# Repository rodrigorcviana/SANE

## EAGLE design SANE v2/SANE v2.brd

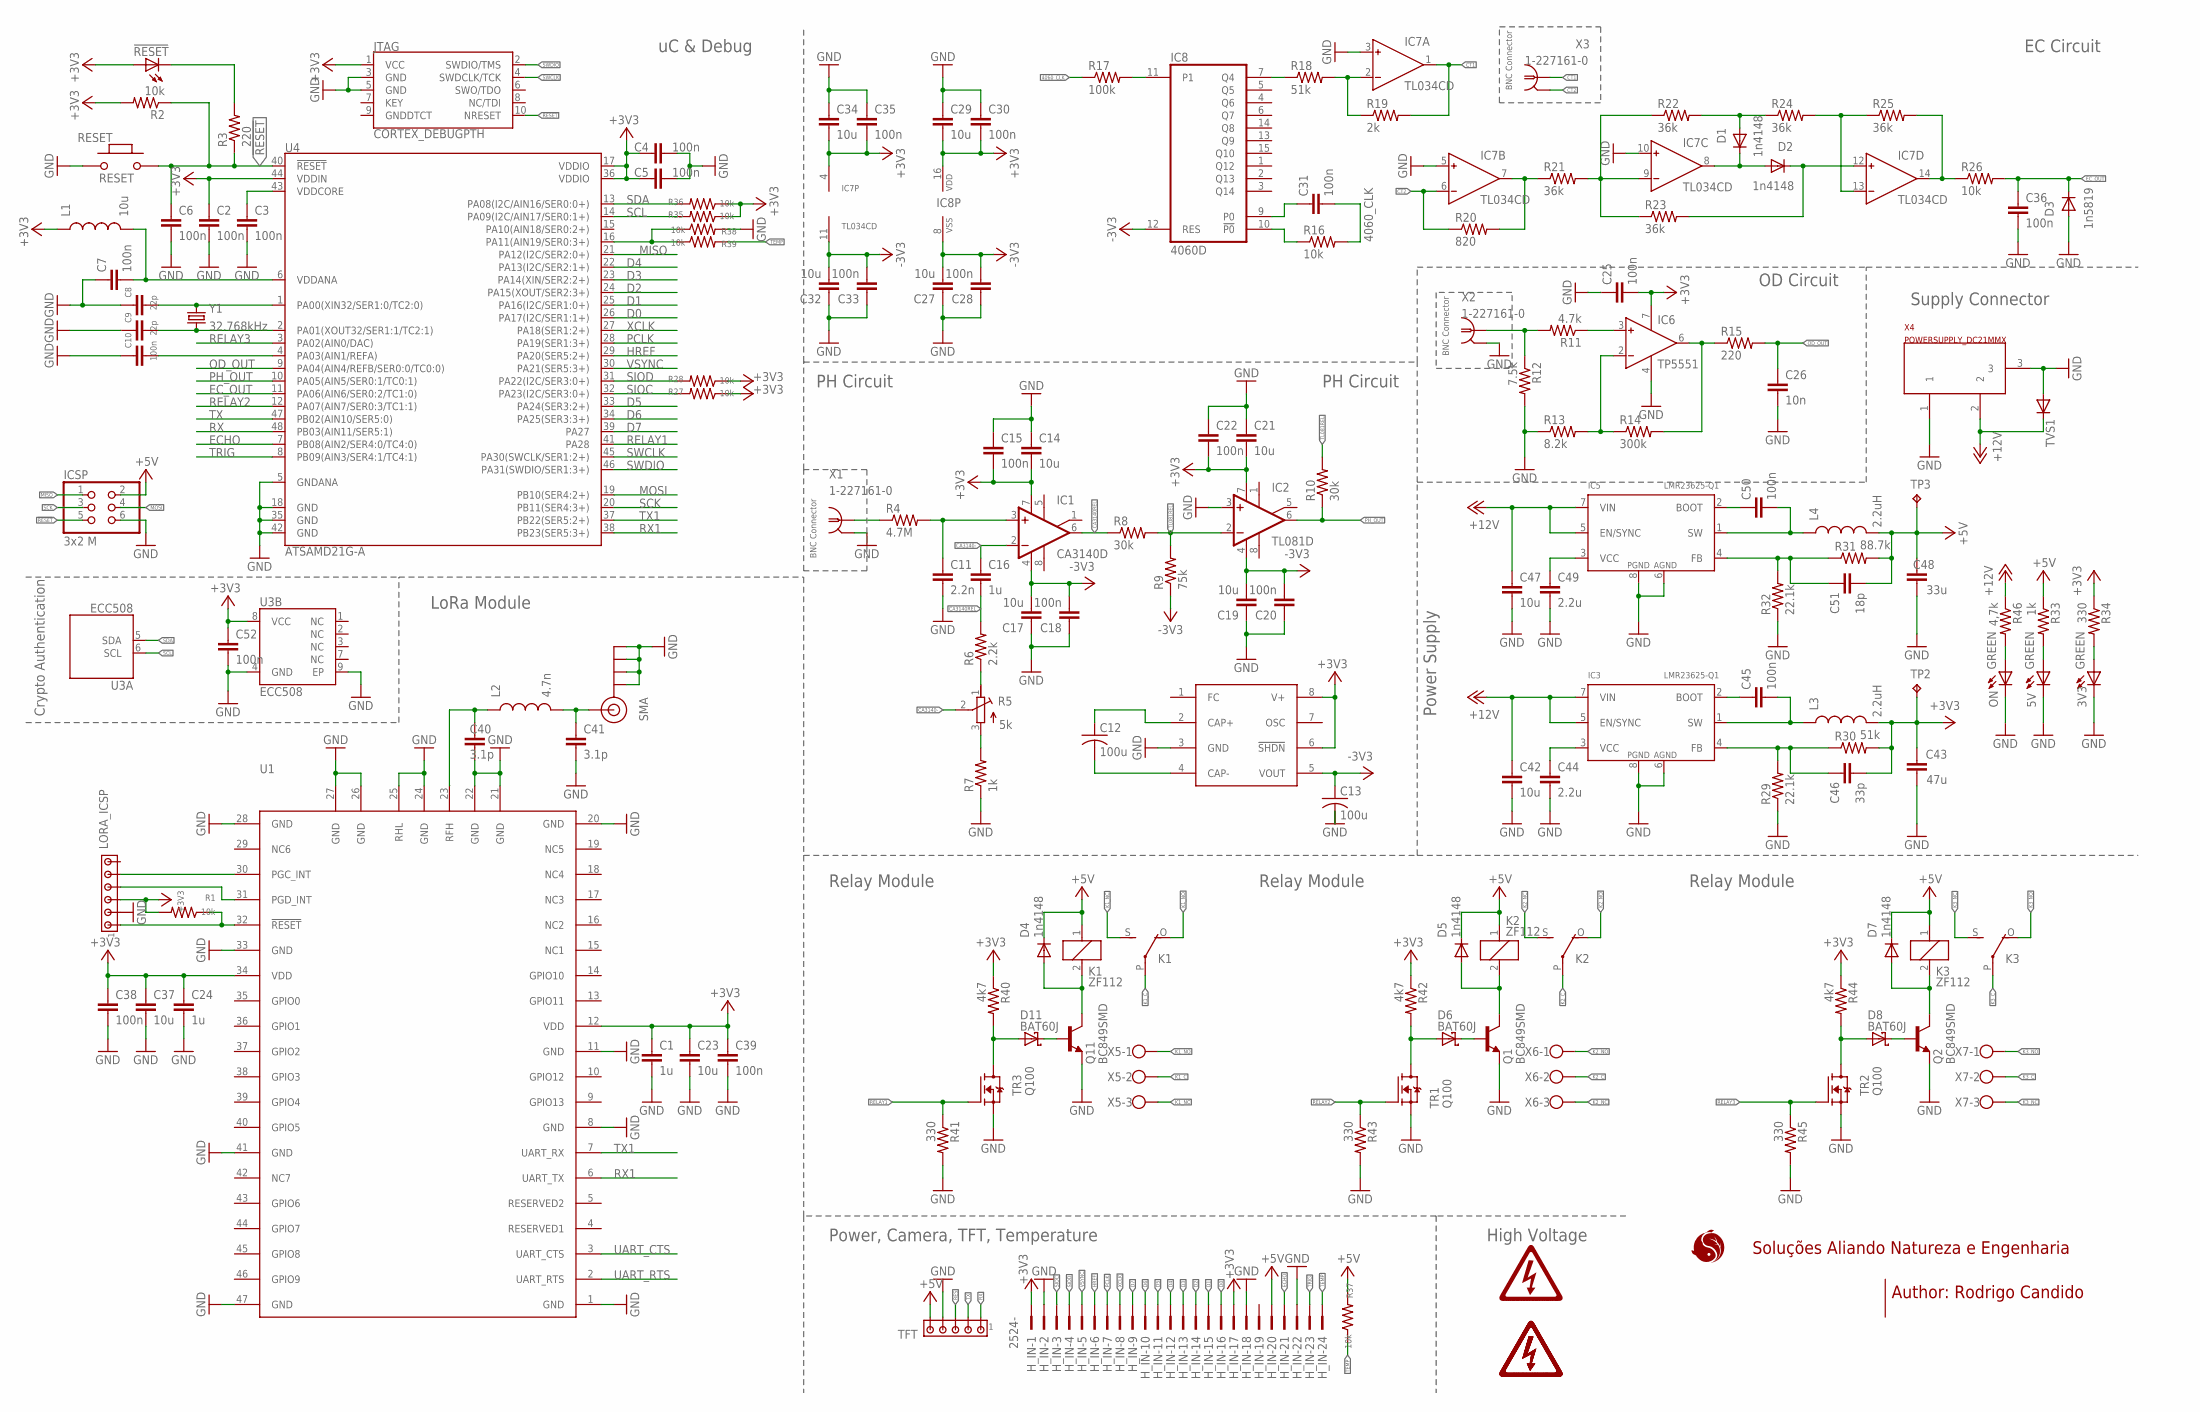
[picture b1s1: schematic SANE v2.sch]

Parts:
3V3, 5V: GREEN; CHIP-LED0805
!RESET: LEDCHIPLED_0805; CHIPLED_0805
C1, C16, C24: 1u; C1206
C2, C3, C4, C5, C6, C7, C10, C15, C18, C20, C22, C25, C28, C30, C31, C33, C35, C36, C38, C39, C45, C50, C52: 100n; C0805
C8, C9: 22p; C0805
C11: 2.2n; C0805
C12, C13: 100u; C1206
C14, C17, C19, C21, C23, C27, C29, C32, C34, C37, C42, C47: 10u; C1206
C26: 10n; C0805
C40, C41: 3.1p; C0603
C43: 47u; C1206
C44, C49: 2.2u; C0805
C46: 33p; C0805
C48: 33u; C1206
C51: 18p; C0805
D1, D2, D4, D5, D7: 1n4148; SOD123
D3: 1n5819; SOD123
D6, D8, D11: BAT60J; SOD323_ST
H_IN: 2524-; PAK100/2500-24
IC1: CA3140D; SO08
IC2: TL081D; SO08
IC3, IC5: LMR23625-Q1; SO08
IC4: TC1121COA; SO8
IC6: TP5551; SO8
IC7: TL034CD; SO14
IC8: 4060D; SO16
ICSP: 3x2 M; 2X03
JTAG: CORTEX_DEBUGPTH; 2X5-PTH-1.27MM
K1, K2, K3: ZF112
L1: 10u; 0603
L2: 4.7n; 0603
L3, L4: 2.2uH; L-NR3010
LORA_ICSP: MTA06-100; 10X06MTA
ON: GREEN; CHIP-LED0805
Q1, Q2, Q11: BC849SMD; SOT23-BEC
R1, R2, R16, R26, R27, R28, R35, R36, R37, R38, R39: 10k; R0805
R3, R15: 220; R0805
R4: 4.7M; R0805
R5: 5k; RTRIMT93YA
R6: 2.2k; R0805
R7, R33: 1k; R0805
R8, R10: 30k; R0805
R9: 75k; R0805
R11: 4.7k; R0805
R12: 7.5k; R0805
R13: 8.2k; R0805
R14: 300k; R0805
R17: 100k; R0805
R18: 51k; R0805
R19: 2k; R0805
R20: 820; R0805
R21, R22, R23, R24, R25: 36k; R0805
R29, R32: 22.1k; R0603
R30: 51k; R0603
R31: 88.7k; R0603
R34, R41, R43, R45: 330; R0805
R40, R42, R44: 4k7; R0805
R46: 4,7k; R0805
RESET: RESET; SMD_157SW
SMA_GPS: SMA_EDGE; SMA-EDGE
TFT: MTA05-100; 10X05MTA
TP2, TP3: TPPAD1-13; P1-13
TR1, TR2, TR3: Q100; SOT-23
TVS1: DIODE-SOD123; SOD123
U1: RN2483/RN2903
U3: ECC508; SON50P300X200X60-9N-EP160X140
U4: ATSAMD21G-A; TQFP-48
U$1, U$2, U$9: SHOCK
U$3: LOGO-SANE
X1, X2, X3: 1-227161-0; AMP_227161
X4: POWERSUPPLY_DC21MMX; POWERSUPPLY_DC-21MM
X5, X6, X7: W237-103
Y1: 32.768kHz; CRYSTAL-SMD-3.2X1.5MM

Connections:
4060_CLK: C31.2, R16.2, R17.1
!RESET: C6.1, ICSP.5, JTAG.10 (NRESET), R2.1, R3.1, RESET.2, U4.40 (!RESET!)
+3V3: !RESET.A, C1.1, C2.1, C4.1, C5.1, C14.2, C15.2, C21.2, C22.2, C23.1, C24.1, C25.2, C29.2, C30.2, C34.2, C35.2, C37.1, C38.1, C39.1, C43.2, C46.2, C52.1, H_IN.1, H_IN.17, IC1.7 (V+), IC2.7 (V+), IC4.6 (!SHDN), IC4.8 (V+), IC6.7 (V+), IC7.4 (V+), IC8.16 (VDD), JTAG.1 (VCC), L1.1, L3.P$2 (2), LORA_ICSP.3, R1.2, R2.2, R27.1, R28.1, R30.2, R34.1, R35.1, R36.1, R40.1, R42.1, R44.1, TP2.TP, U1.12 (VDD), U1.34 (VDD), U3.8 (VCC), U4.17 (VDDIO), U4.36 (VDDIO), U4.44 (VDDIN)
+5V: C48.2, C51.2, D4.C, D5.C, D7.C, H_IN.20, ICSP.2, K1.1, K2.1, K3.1, L4.P$2 (2), R31.2, R33.1, R37.2, TFT.5, TP3.TP
+12V: C42.1, C47.1, IC3.5 (EN/SYNC), IC3.7 (VIN), IC5.5 (EN/SYNC), IC5.7 (VIN), R46.1, TVS1.C, X4.2
-3V3: C13.1, C17.2, C18.2, C19.2, C20.2, C27.2, C28.2, C32.2, C33.2, IC1.4 (V-), IC2.4 (V-), IC4.5 (VOUT), IC7.11 (V-), IC8.8 (VSS), IC8.12 (RES), R9.1
CA3140-: C16.1, IC1.2 (-IN), R5.2 (S)
CA3140REL: C16.2, IC1.6 (OUT), R6.2, R8.1
CT1: IC7.1 (OUT), R19.2, X3.1
CT2: IC7.6 (IN-), R20.1, X3.2
D0: H_IN.16, U4.26 (PA17(I2C/SER1:1+))
D1: H_IN.15, U4.25 (PA16(I2C/SER1:0+))
D2: H_IN.14, U4.24 (PA15(XOUT/SER2:3+))
D3: H_IN.13, U4.23 (PA14(XIN/SER2:2+))
D4: H_IN.12, U4.22 (PA13(I2C/SER2:1+))
D5: H_IN.11, U4.33 (PA24(SER3:2+))
D6: H_IN.10, U4.34 (PA25(SER3:3+))
D7: H_IN.9, U4.39 (PA27)
ECHO: H_IN.21, U4.7 (PB08(AIN2/SER4:0/TC4:0))
EC_OUT: C36.1, D3.C, R26.2, U4.11 (PA06(AIN6/SER0:2/TC1:0))
GND: 3V3.C, 5V.C, C1.2, C2.2, C3.2, C4.2, C5.2, C6.2, C7.1, C8.1, C9.1, C10.1, C11.2, C13.2, C14.1, C15.1, C17.1, C18.1, C19.1, C20.1, C21.1, C22.1, C23.2, C24.2, C25.1, C26.2, C27.1, C28.1, C29.1, C30.1, C32.1, C33.1, C34.1, C35.1, C36.2, C37.2, C38.2, C39.2, C40.2, C41.2, C42.2, C43.1, C44.2, C47.2, C48.1, C49.2, C52.2, D3.A, H_IN.2, H_IN.18, H_IN.22, IC2.3 (+IN), IC3.6 (AGND), IC3.8 (PGND), IC4.3 (GND), IC5.6 (AGND), IC5.8 (PGND), IC6.4 (V-), IC7.3 (IN+), IC7.5 (IN+), IC7.10 (IN+), ICSP.6, JTAG.3 (GND), JTAG.5 (GND), LORA_ICSP.2, ON.C, Q1.E, Q2.E, Q11.E, R7.1, R12.2, R13.1, R29.1, R32.1, R38.2, R41.2, R43.2, R45.2, RESET.1, SMA_GPS.GND@0 (GND), SMA_GPS.GND@1 (GND), SMA_GPS.GND@2 (GND), SMA_GPS.GND@3 (GND), TFT.4, TR1.2 (S), TR2.2 (S), TR3.2 (S), TVS1.A, U1.1 (GND), U1.8 (GND), U1.11 (GND), U1.20 (GND), U1.21 (GND), U1.22 (GND), U1.24 (GND), U1.25 (RHL), U1.26 (GND), U1.27 (GND), U1.28 (GND), U1.33 (GND), U1.41 (GND), U1.47 (GND), U3.4 (GND), U3.9 (EP), U4.5 (GNDANA), U4.18 (GND), U4.35 (GND), U4.42 (GND), X1.2, X2.2, X4.1, X4.3
HREF: H_IN.6, U4.29 (PA20(SER5:2+))
K1_C: K1.P, X5.2
K1_NC: K1.S, X5.3
K1_NO: K1.O, X5.1
K2_C: K2.P, X6.2
K2_NC: K2.S, X6.3
K2_NO: K2.O, X6.1
K3_C: K3.P, X7.2
K3_NC: K3.S, X7.3
K3_NO: K3.O, X7.1
MISO: ICSP.1, U4.21 (PA12(I2C/SER2:0+))
MOSI: ICSP.4, U4.19 (PB10(SER4:2+))
unnamed: C3.1, U4.43 (VDDCORE)
unnamed: C8.2, U4.1 (PA00(XIN32/SER1:0/TC2:0)), Y1.P$2 (2)
unnamed: C10.2, U4.4 (PA03(AIN1/REFA))
unnamed: !RESET.C, R3.2
unnamed: C9.2, U4.2 (PA01(XOUT32/SER1:1/TC2:1)), Y1.P$1 (1)
unnamed: C7.2, L1.2, U4.6 (VDDANA)
unnamed: R4.1, X1.1
unnamed: C11.1, IC1.3 (+IN), R4.2
unnamed: C12.1, IC4.2 (CAP+)
unnamed: C12.2, IC4.4 (CAP-)
unnamed: R11.2, R12.1, X2.1
unnamed: IC6.3 (IN+), R11.1
unnamed: R5.1 (E), R6.1
unnamed: R5.3 (A), R7.2
unnamed: IC8.10 (!P0), R16.1
unnamed: IC6.2 (IN-), R13.2, R14.1
unnamed: IC6.6 (OUT), R14.2, R15.1
unnamed: C31.1, IC8.9 (P0)
unnamed: IC7.2 (IN-), R18.2, R19.1
unnamed: IC8.11 (P1), R17.2
unnamed: IC8.7 (Q4), R18.1
unnamed: IC7.9 (IN-), R21.2, R22.1, R23.1
unnamed: IC7.7 (OUT), R20.2, R21.1
unnamed: D1.A, R22.2, R24.1
unnamed: D1.C, D2.A, IC7.8 (OUT)
unnamed: D2.C, IC7.12 (IN+), R23.2
unnamed: IC7.13 (IN-), R24.2, R25.1
unnamed: IC7.14 (OUT), R25.2, R26.1
unnamed: LORA_ICSP.1, R1.1, U1.32 (!RESET)
unnamed: LORA_ICSP.5, U1.30 (PGC_INT)
unnamed: LORA_ICSP.4, U1.31 (PGD_INT)
unnamed: C40.1, L2.1, U1.23 (RFH)
unnamed: C41.1, L2.2, SMA_GPS.SIG (SIGNAL)
unnamed: C44.1, IC3.3 (VCC)
unnamed: C45.1, IC3.2 (BOOT)
unnamed: C45.2, IC3.1 (SW), L3.P$1 (1)
unnamed: C46.1, IC3.4 (FB), R29.2, R30.1
unnamed: C49.1, IC5.3 (VCC)
unnamed: C50.1, IC5.2 (BOOT)
unnamed: C50.2, IC5.1 (SW), L4.P$1 (1)
unnamed: C51.1, IC5.4 (FB), R31.1, R32.2
unnamed: 5V.A, R33.2
unnamed: 3V3.A, R34.2
unnamed: R38.1, R39.1, U4.16 (PA11(AIN19/SER0:3+))
unnamed: D11.A, R40.2, TR3.1 (D)
unnamed: D11.C, Q11.B
unnamed: D4.A, K1.2, Q11.C
unnamed: D6.A, R42.2, TR1.1 (D)
unnamed: D6.C, Q1.B
unnamed: D5.A, K2.2, Q1.C
unnamed: D8.A, R44.2, TR2.1 (D)
unnamed: D8.C, Q2.B
unnamed: D7.A, K3.2, Q2.C
unnamed: ON.A, R46.2
OD_OUT: C26.1, R15.2, U4.9 (PA04(AIN4/REFB/SER0:0/TC0:0))
PCLK: H_IN.7, U4.28 (PA19(SER1:3+))
PH_OUT: IC2.6 (OUT), R10.1, U4.10 (PA05(AIN5/SER0:1/TC0:1))
RELAY1: R41.1, TR3.3 (G), U4.41 (PA28)
RELAY2: R43.1, TR1.3 (G), U4.12 (PA07(AIN7/SER0:3/TC1:1))
RELAY3: R45.1, TR2.3 (G), U4.3 (PA02(AIN0/DAC))
RES: TFT.3
RX: TFT.1, U4.48 (PB03(AIN11/SER5:1))
RX1: U1.6 (UART_TX), U4.38 (PB23(SER5:3+))
SCK: ICSP.3, U4.20 (PB11(SER4:3+))
SCL: R35.2, U3.6 (SCL), U4.14 (PA09(I2C/AIN17/SER0:1+))
SDA: R36.2, U3.5 (SDA), U4.13 (PA08(I2C/AIN16/SER0:0+))
SIOC: H_IN.3, R27.2, U4.32 (PA23(I2C/SER3:0+))
SIOD: H_IN.4, R28.2, U4.31 (PA22(I2C/SER3:0+))
SWCLK: JTAG.4 (SWDCLK/TCK), U4.45 (PA30(SWCLK/SER1:2+))
SWDIO: JTAG.2 (SWDIO/TMS), U4.46 (PA31(SWDIO/SER1:3+))
TEMP: H_IN.24, R37.1, R39.2
TL081REL: IC2.2 (-IN), R8.2, R9.2, R10.2
TRIG: H_IN.23, U4.8 (PB09(AIN3/SER4:1/TC4:1))
TX: TFT.2, U4.47 (PB02(AIN10/SER5:0))
TX1: U1.7 (UART_RX), U4.37 (PB22(SER5:2+))
UART_CTS: U1.3 (UART_CTS)
UART_RTS: U1.2 (UART_RTS)
VSYNC: H_IN.5, U4.30 (PA21(SER5:3+))
XCLK: H_IN.8, U4.27 (PA18(SER1:2+))

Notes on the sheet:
SMA
uC & Debug
Power, Camera, TFT, Temperature
LoRa Module
Crypto Authentication
EC Circuit
PH Circuit
OD Circuit
High Voltage
Relay Module
Power Supply
Supply Connector
BNC Connector
Soluções Aliando Natureza e Engenharia
Author: Rodrigo Candido

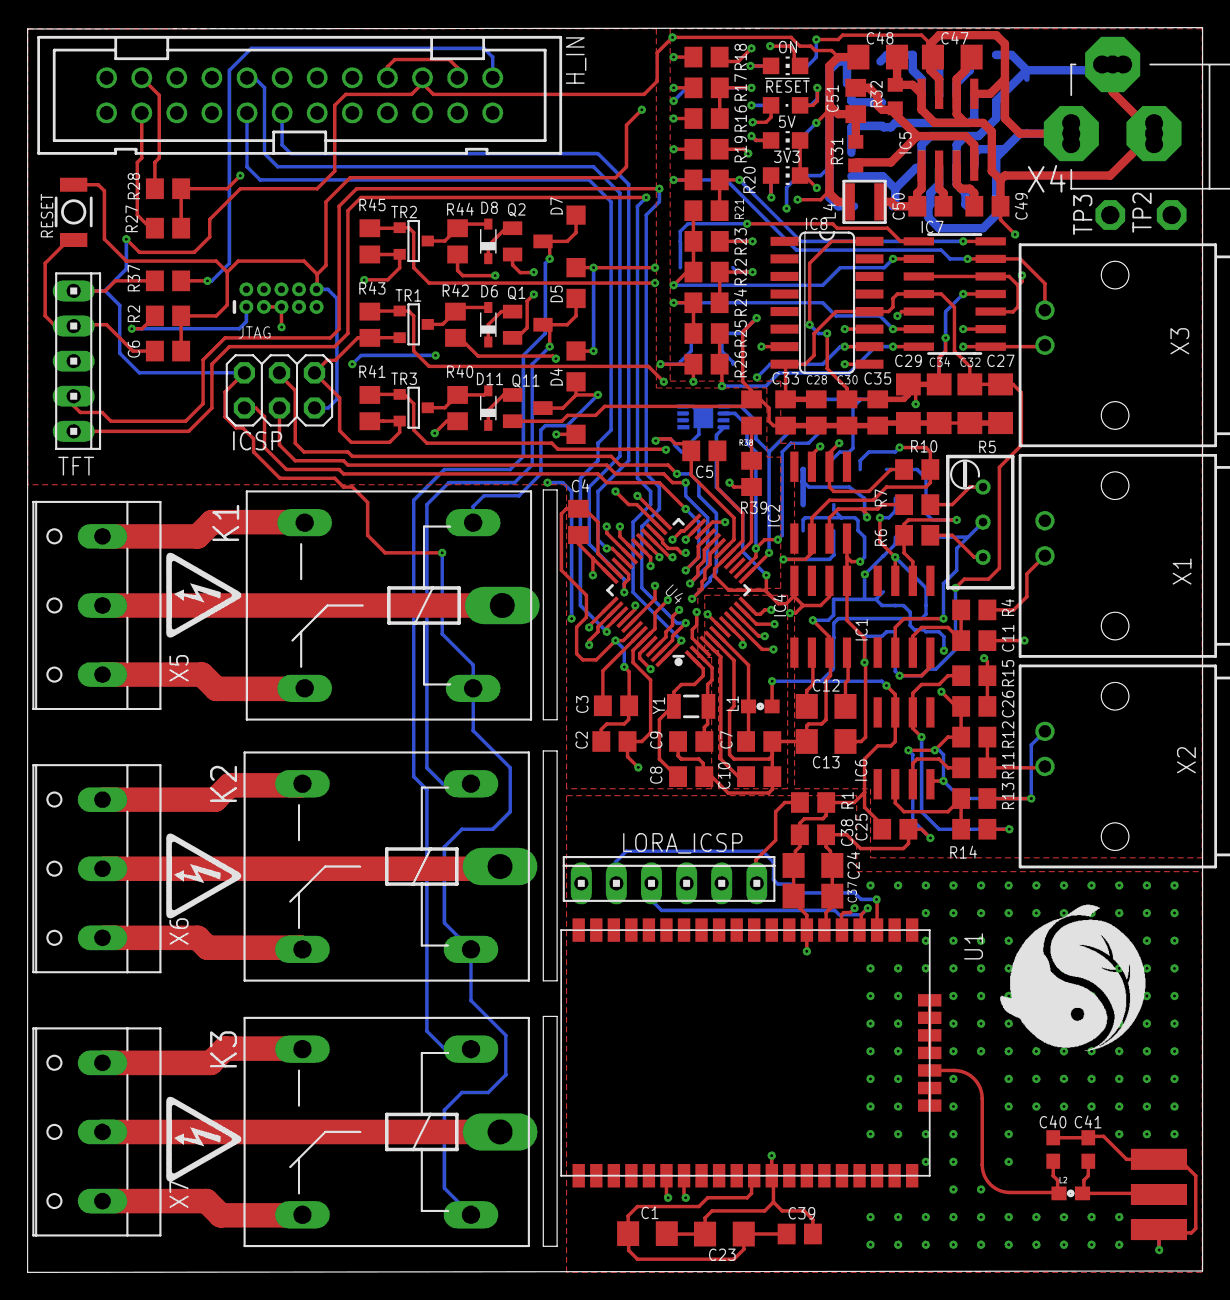
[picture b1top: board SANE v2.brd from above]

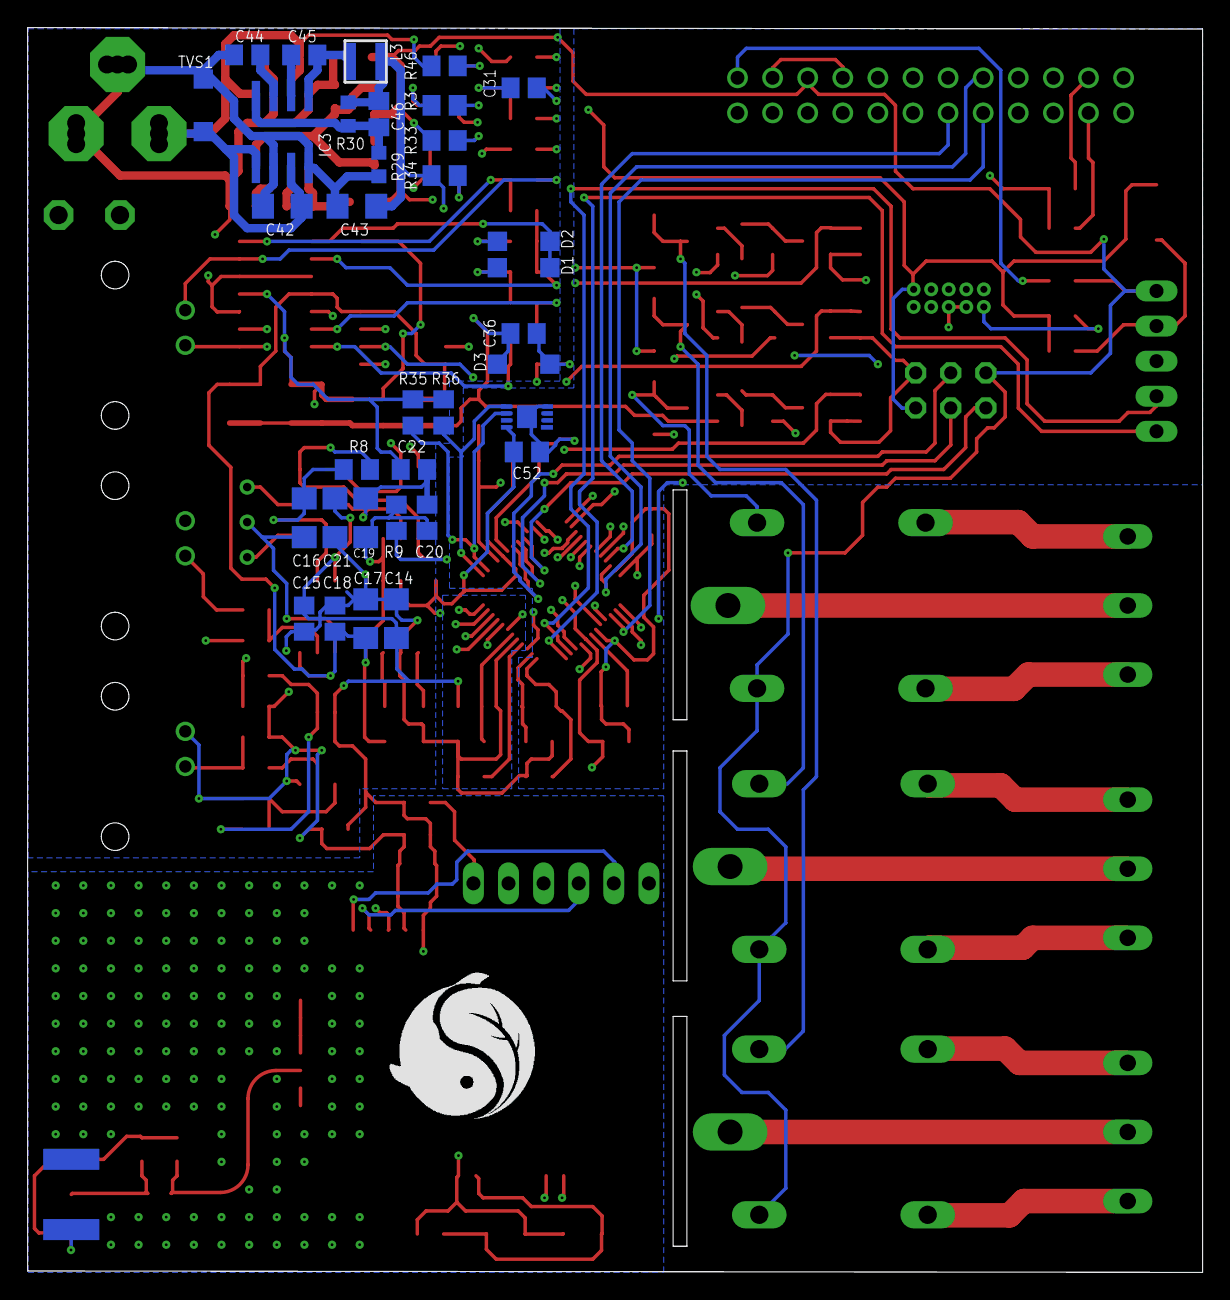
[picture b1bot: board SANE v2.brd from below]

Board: 4 copper layers, 85.0 x 90.1 mm, 158 parts (35 on the bottom side), 109 nets.

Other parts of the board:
U$4: LOGO-SANE

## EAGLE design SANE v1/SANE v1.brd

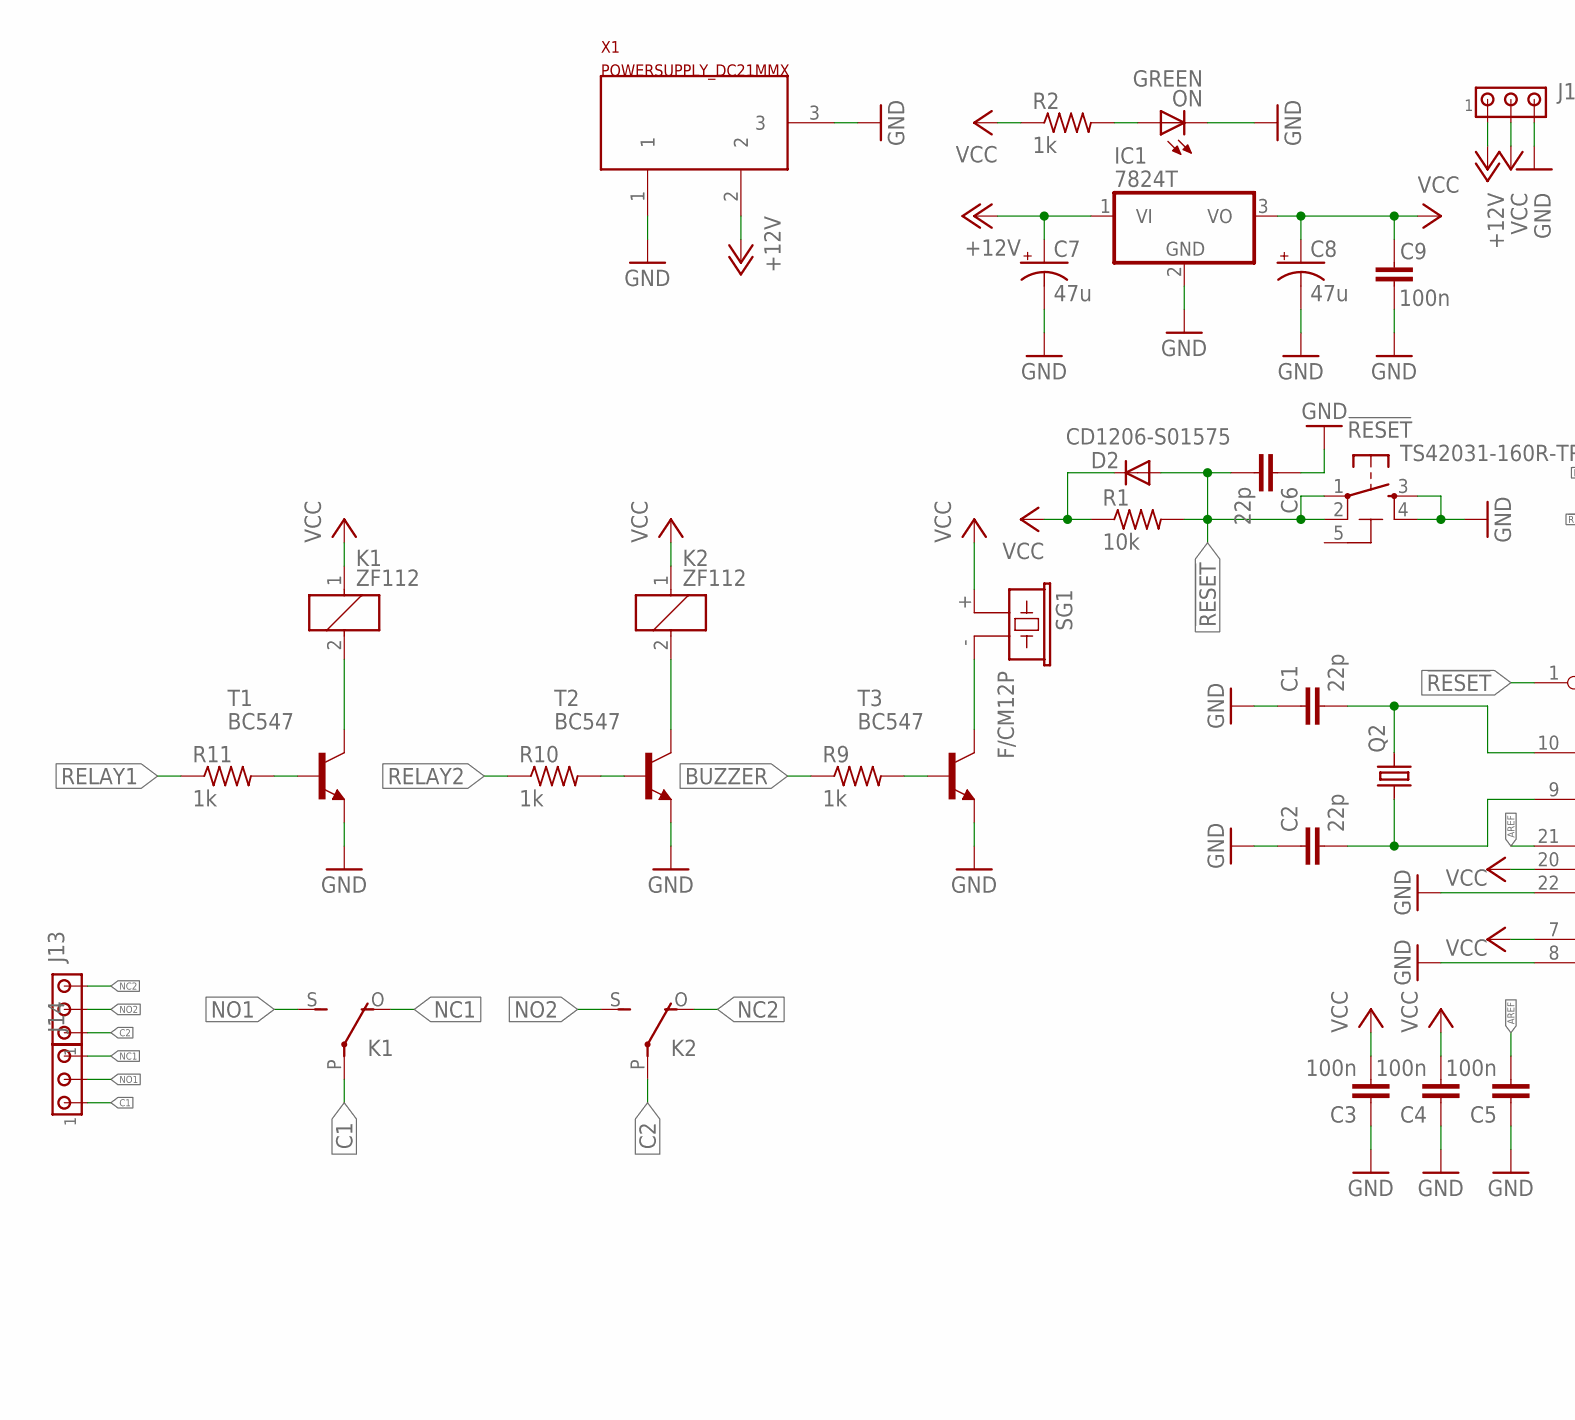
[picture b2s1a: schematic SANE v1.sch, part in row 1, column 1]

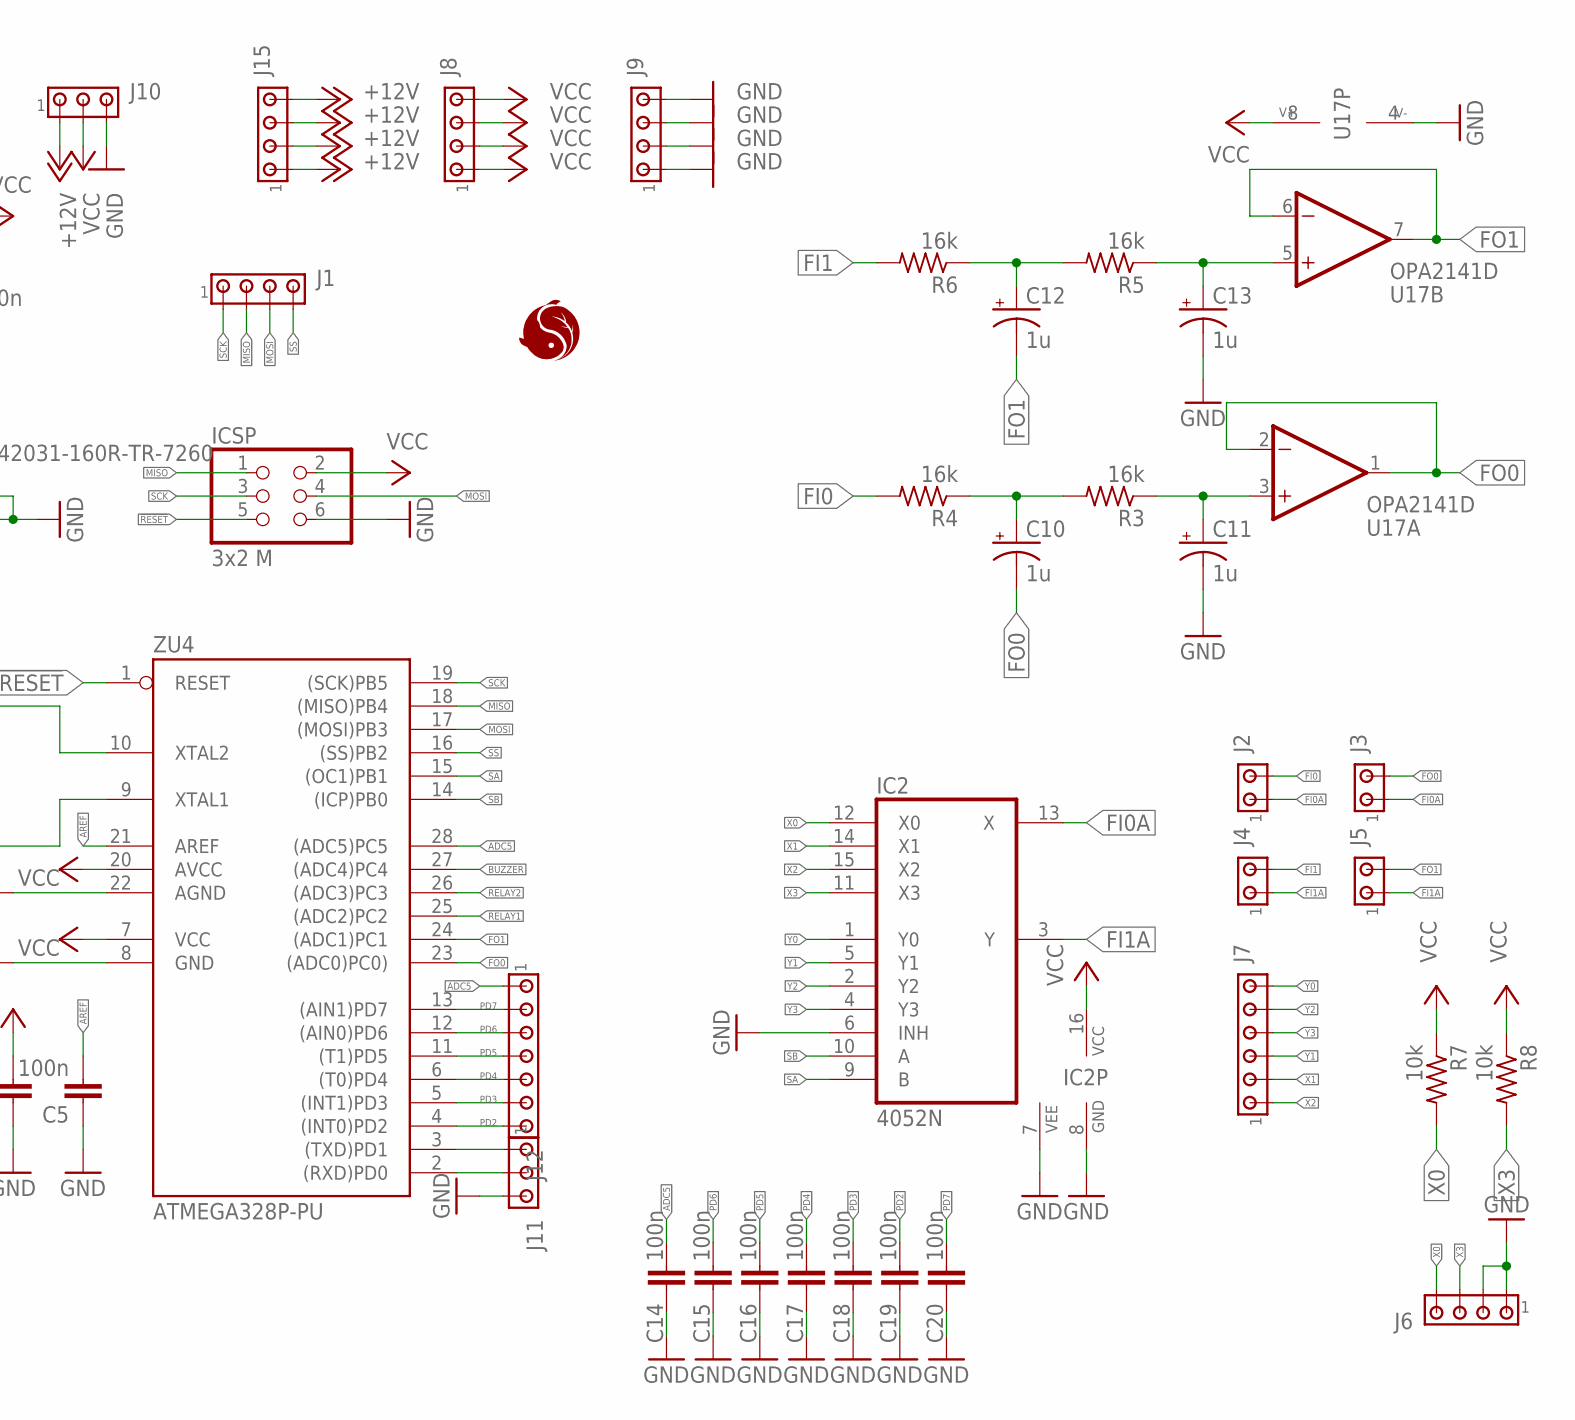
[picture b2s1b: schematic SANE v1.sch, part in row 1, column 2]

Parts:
!RESET: TS42031-160R-TR-7260; TS42
C1, C2, C6: 22p; C0805
C3, C4, C5, C9, C14, C15, C16, C17, C18, C19, C20: 100n; C0805
C7, C8: 47u; E2-4
C10, C11, C12, C13: 1u; E2-4
D2: CD1206-S01575; MINIMELF
IC1: 7824T; TO220H
IC2: 4052N; DIL16
ICSP: 3x2 M; 2X03
J1, J6, J8, J9, J15: MTA04-100; 10X04MTA
J2, J3, J4, J5: MTA02-100; 10X02MTA
J7: MTA06-100; 10X06MTA
J10, J11: MTA03-100; 10X03MTA
J12: MTA07-100; 10X07MTA
J13, J14: MTA03-156; 1X3MTA
K1, K2: ZF112
ON: GREEN; CHIP-LED0805
Q2: CRYSTALHC49U-V; HC49U-V
R1, R7, R8: 10k; R0805
R2, R9, R10, R11: 1k; R0805
R3, R4, R5, R6: 16k; R0805
SG1: F/CM12P
T1, T2, T3: BC547; TO92
U17: OPA2141D; SO08
U$1: LOGO-SANE
X1: POWERSUPPLY_DC21MMX; POWERSUPPLY_DC-21MM
ZU4: ATMEGA328P-PU; DIL28-3

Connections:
5-GND: !RESET.5 (5-GND)
!RESET: !RESET.1, !RESET.2, C6.2, D2.A, ICSP.5, R1.2, ZU4.1 (RESET)
+12V: C7.+, IC1.1 (VI), J10.1, J15.1, J15.2, J15.3, J15.4, X1.2
ADC5: C14.2, J12.1, ZU4.28 ((ADC5)PC5)
AREF: C5.2, ZU4.21 (AREF)
BUZZER: R9.1, ZU4.27 ((ADC4)PC4)
C1: J14.1, K1.P
C2: J13.1, K2.P
FI0: J2.2, R4.2
FI0A: IC2.13 (X), J2.1, J3.1
FI1: J4.2, R6.2
FI1A: IC2.3 (Y), J4.1, J5.1
FO0: C10.-, J3.2, U17.1 (OUT), U17.2 (-IN), ZU4.23 ((ADC0)PC0))
FO1: C12.-, J5.2, U17.6 (-IN), U17.7 (OUT), ZU4.24 ((ADC1)PC1)
GND: !RESET.3, !RESET.4, C1.1, C2.1, C3.1, C4.1, C5.1, C6.1, C7.-, C8.-, C9.1, C11.-, C13.-, C14.1, C15.1, C16.1, C17.1, C18.1, C19.1, C20.1, IC1.2 (GND), IC2.6 (INH), IC2.7 (VEE), IC2.8 (GND), ICSP.6, J6.1, J6.2, J9.1, J9.2, J9.3, J9.4, J10.3, J11.3, ON.C, T1.1 (E), T2.1 (E), T3.1 (E), U17.4 (V-), X1.1, X1.3, ZU4.8 (GND), ZU4.22 (AGND)
MISO: ICSP.1, J1.2, ZU4.18 ((MISO)PB4)
MOSI: ICSP.4, J1.3, ZU4.17 ((MOSI)PB3)
unnamed: C1.2, Q2.2, ZU4.10 (XTAL2)
unnamed: C2.2, Q2.1, ZU4.9 (XTAL1)
unnamed: ON.A, R2.2
unnamed: C11.+, R3.1, U17.3 (+IN)
unnamed: C10.+, R3.2, R4.1
unnamed: C12.+, R5.2, R6.1
unnamed: C13.+, R5.1, U17.5 (+IN)
unnamed: J11.1, ZU4.3 ((TXD)PD1)
unnamed: J11.2, ZU4.2 ((RXD)PD0)
unnamed: SG1.- (2), T3.3 (C)
unnamed: K1.2, T1.3 (C)
unnamed: K2.2, T2.3 (C)
unnamed: R11.2, T1.2 (B)
unnamed: R10.2, T2.2 (B)
unnamed: R9.2, T3.2 (B)
NC1: J14.3, K1.O
NC2: J13.3, K2.O
NO1: J14.2, K1.S
NO2: J13.2, K2.S
PD2: C19.2, J12.7, ZU4.4 ((INT0)PD2)
PD3: C18.2, J12.6, ZU4.5 ((INT1)PD3)
PD4: C17.2, J12.5, ZU4.6 ((T0)PD4)
PD5: C16.2, J12.4, ZU4.11 ((T1)PD5)
PD6: C15.2, J12.3, ZU4.12 ((AIN0)PD6)
PD7: C20.2, J12.2, ZU4.13 ((AIN1)PD7)
RELAY1: R11.1, ZU4.25 ((ADC2)PC2)
RELAY2: R10.1, ZU4.26 ((ADC3)PC3)
SA: IC2.9 (B), ZU4.15 ((OC1)PB1)
SB: IC2.10 (A), ZU4.14 ((ICP)PB0)
SCK: ICSP.3, J1.1, ZU4.19 ((SCK)PB5)
SS: J1.4, ZU4.16 ((SS)PB2)
VCC: C3.2, C4.2, C8.+, C9.2, D2.C, IC1.3 (VO), IC2.16 (VCC), ICSP.2, J8.1, J8.2, J8.3, J8.4, J10.2, K1.1, K2.1, R1.1, R2.1, R7.1, R8.1, SG1.+ (1), U17.8 (V+), ZU4.7 (VCC), ZU4.20 (AVCC)
X0: IC2.12 (X0), J6.4, R7.2
X1: IC2.14 (X1), J7.2
X2: IC2.15 (X2), J7.1
X3: IC2.11 (X3), J6.3, R8.2
Y0: IC2.1 (Y0), J7.6
Y1: IC2.5 (Y1), J7.3
Y2: IC2.2 (Y2), J7.5
Y3: IC2.4 (Y3), J7.4

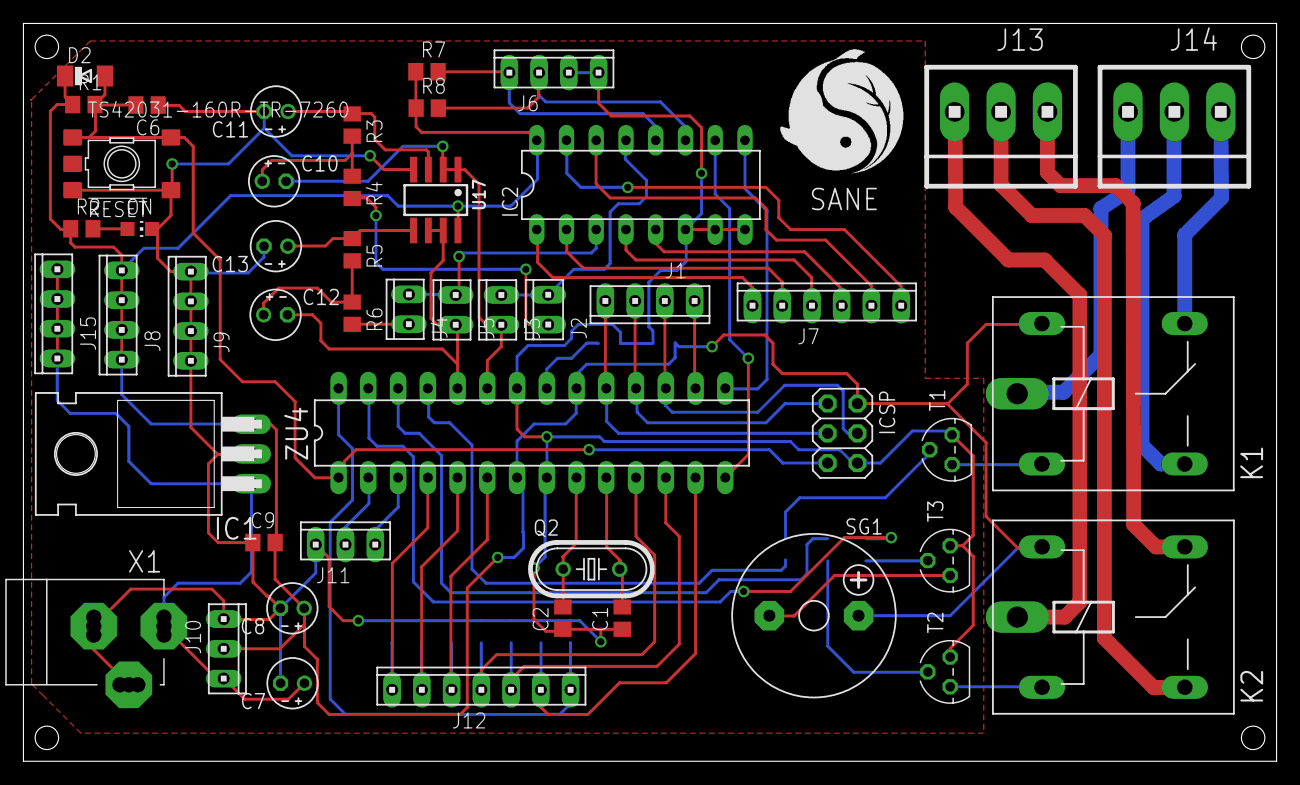
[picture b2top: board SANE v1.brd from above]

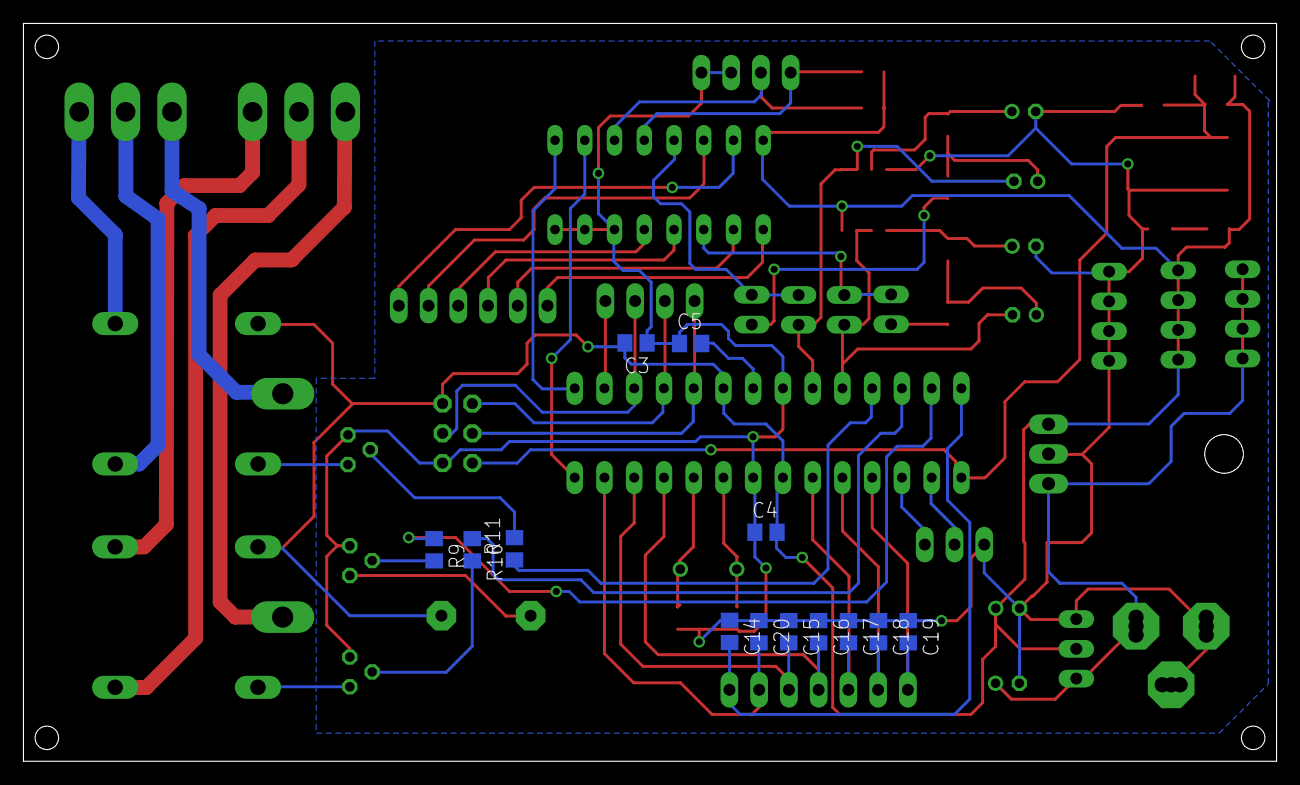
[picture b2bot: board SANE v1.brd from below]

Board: 2 copper layers, 107.0 x 63.0 mm, 63 parts (13 on the bottom side), 56 nets.

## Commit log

2021-04-13 update files

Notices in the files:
parts and their libraries:
amp-op: Copyright (C) 2015, Bob Starr
SparkFun-Passives: Licensing: Creative Commons ShareAlike 4.0 International - https://creativecommons.org/licenses/by-sa/4.0
